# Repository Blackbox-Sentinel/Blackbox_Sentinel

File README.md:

# 🛡️ BlackBox Sentinel

> **Autonomous Physical Network Intrusion Prevention Appliance & Immutable Ledger**  
> *Raspberry Pi 4 • Layer-2 Inline Bridge • Isolation Forest ML • Physical Relay Air-Gap • Cellular Alerting • 3D CAD Twin & Ubuntu Kiosk*

---

## 📋 System Overview

**BlackBox Sentinel** is a production-grade physical cyber defense appliance deployed inline on local network segments. It inspects live network traffic, flags zero-day anomalies using an Isolation Forest ML pipeline, physically isolates the network via a high-speed mechanical relay upon confirmed breach, zeroizes cryptographic keys upon chassis tamper detection, and records forensic evidence to an immutable SHA-256 hash-chained ledger.

---

## 🏗️ 4-Module Architecture

```
┌──────────────────────────────────────────────────────────────────────────────────────────┐
│                                   BlackBox Sentinel                                      │
├──────────────────────┬──────────────────────┬──────────────────────┬─────────────────────┤
│   M1 • Hardware/HAL  │   M2 • Systems/OS    │   M3 • ML & Ledger   │   M4 • GUI & 3D Twin│
│                      │                      │                      │                     │
│ • Raspberry Pi 4 B   │ • Layer-2 Bridge br0 │ • Isolation Forest   │ • Ubuntu Kiosk OS   │
│ • Songle 5V Relay    │ • OverlayFS RO Root  │ • Feature Extraction │ • 3D CAD Studio     │
│ • ESP32 Co-processor │ • systemd Services   │ • SHA-256 Hash Chain │ • Circuit Simulator │
│ • SIM800L Cellular   │ • Veth Sim Lab       │ • Anti-Tamper Wiping │ • REST API Server   │
└──────────────────────┴──────────────────────┴──────────────────────┴─────────────────────┘
```

---

## 👥 Multi-Developer Workspace Sharing (Antigravity & Visual Studio Code)

This repository includes a multi-developer workspace setup for **Antigravity** and **Visual Studio Code**:

1. **One-Click Workspace**: Open `blackbox-sentinel.code-workspace` in Antigravity / VS Code to automatically load all submodules with pre-tuned settings.
2. **1-Click Debuggers (F5)**:
   - `🚀 Run Sentinel Pipeline (Sim Mode + GUI)`
   - `🌐 Start Ubuntu Web Kiosk & 3D CAD Studio`
   - `⚡ Start Hardware Bridge Simulator Server`
   - `🧠 Train Isolation Forest & Ledger (M3)`
   - `🔬 Run Pytest Suite`
3. **Live Share Pair-Programming**: Configured via `.vsls.json` to automatically tunnel ports `8080` (Web UI/CAD) and `5000` (API) between teammates across the internet.
4. **Automated Workspace Sync**: Run `python sync_workspace.py` or double-click `setup_workspace.bat` (Windows) / `setup_workspace.sh` (Linux/macOS).

*Refer to [WORKSPACE_SHARING_GUIDE.md](WORKSPACE_SHARING_GUIDE.md) for full team onboarding instructions.*

---

## 🚀 Quick Start

### 1. Installation
```bash
git clone https://github.com/Blackbox-Sentinel/Blackbox_Sentinel.git
cd Blackbox_Sentinel

# Windows setup:
setup_workspace.bat

# Linux / macOS setup:
chmod +x setup_workspace.sh && ./setup_workspace.sh
```

### 2. Run the Phase 2 Software Vertical Slice

Run the normalized M2/M3 telemetry producer in one terminal:

```bash
python3 integration/phase2_vertical_slice.py \\
  --output m3-ml-ledger/data/phase2_telemetry.jsonl
```

Run the canonical 480×320 M4 touchscreen dashboard in a second terminal:

```bash
python3 gui/dashboard.py \\
  --telemetry-file m3-ml-ledger/data/phase2_telemetry.jsonl
```

The slice demonstrates calibration, normal traffic, pending evidence, approved containment, replay/stale rejection, quorum conflict, receipt audit, and recovery-required states. It is software simulation only; ESP32 physical enforcement still requires M1 validation.

### 3. Other Entry Points

```bash
# Larger M4 desktop simulation GUI:
python3 m4-gui-venture/src/app.py

# Optional browser kiosk prototype:
python3 m4-gui-venture/server.py

# Legacy core pipeline without normalized Phase 2 integration:
python3 sentinel_pipeline.py
```

### 4. Open Interactive 3D CAD Studio & Ubuntu Kiosk
- **Ubuntu 24.04 Kiosk Desktop**: [http://localhost:8080/](http://localhost:8080/)
- **3D CAD Hardware Studio**: [http://localhost:8080/cad_viewer.html](http://localhost:8080/cad_viewer.html)
- **Virtual Circuit Simulator**: [http://localhost:8080/simulator.html](http://localhost:8080/simulator.html)

---

## 📁 Repository Structure

The Phase 2 integration files are under `integration/`, with the detailed runbook in [`docs/Phase2_Vertical_Slice.md`](docs/Phase2_Vertical_Slice.md).

```text
Blackbox_Sentinel/
├── blackbox-sentinel.code-workspace  # Multi-root workspace for Antigravity & VS Code
├── WORKSPACE_SHARING_GUIDE.md        # Team collaboration & Live Share instructions
├── sync_workspace.py                 # Cross-platform environment diagnostic tool
├── setup_workspace.bat / .sh         # 1-click workspace bootstrap scripts
├── requirements.txt                  # Consolidated Python dependencies
├── sentinel_pipeline.py              # Unified pipeline entrypoint (Sim / Real)
│
├── common/                           # Universal Hardware Abstraction Layer (HAL)
│   └── hal/                          # Drivers for Real GPIO / Virtual Simulation
│
├── m1-hardware/                      # Hardware schematics, ESP32 firmware, Wokwi
│   ├── src/esp32_coprocessor.ino     # ESP-NOW mesh co-processor firmware
│   └── wokwi/                        # Interactive Wokwi circuit simulation
│
├── m2-systems/                       # Operating system, bridge config, Docker lab
│   ├── os/                           # OverlayFS root, security hardening, systemd
│   └── sim/                          # Virtual network namespace lab & traffic gen
│
├── m3-ml-ledger/                     # Machine learning & immutable cryptographic ledger
│   ├── src/                          # Isolation Forest training, inference & ledger
│   └── models/                       # Seed trained model weights
│
└── m4-gui-venture/                   # Web Kiosk OS, 3D CAD Studio & API Backends
    ├── server.py                     # Kiosk Web Server (Port 8080)
    ├── hw_simulator_server.py        # Hardware Bridge REST API (Port 5000)
    └── web/                          # PBR Three.js 3D CAD Viewer & OS GUI
```

---

## 🔒 Security Hardening & Hardware Defense

- **Mechanical Air-Gap Relay**: Disconnects Ethernet physically within $<15\text{ms}$ upon threat classification.
- **Active Tamper Mesh**: Copper grid monitored via continuous GPIO pull-down interrupt; triggers zeroization of cryptographic memory within $10\mu\text{s}$.
- **Immutable Ledger**: Every network packet feature hash is chained using SHA-256 with nonce and timestamp verification.

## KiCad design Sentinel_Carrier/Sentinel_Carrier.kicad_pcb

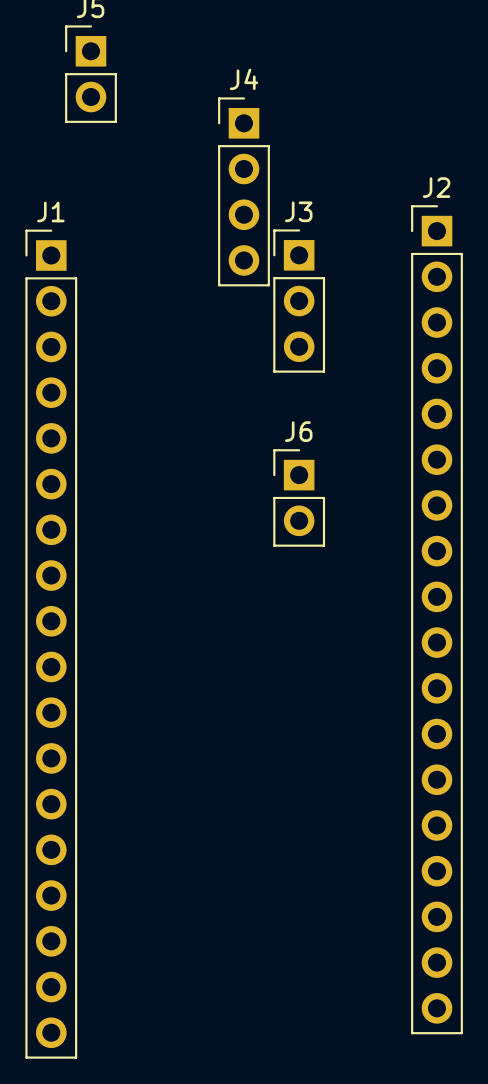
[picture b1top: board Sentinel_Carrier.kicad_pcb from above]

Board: 2 copper layers, 6 parts (0 on the bottom side), 7 nets, no tracks yet.

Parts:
J1: ESP32_Left; PinHeader_1x18_P2.54mm_Vertical
J2: ESP32_Right; PinHeader_1x18_P2.54mm_Vertical
J3: Relay; PinHeader_1x03_P2.54mm_Vertical
J4: PiBridge; PinHeader_1x04_P2.54mm_Vertical
J5: Tamper1; PinHeader_1x02_P2.54mm_Vertical
J6: Tamper2; PinHeader_1x02_P2.54mm_Vertical

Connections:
5V: J1.1, J3.1, J4.1
ESP_RX: J2.16, J4.3
ESP_TX: J2.17, J4.4
GND: J1.2, J3.2, J4.2, J5.2, J6.2
RELAY_IN: J2.4, J3.3
TAMPER1: J2.5, J5.1
TAMPER2: J2.6, J6.1
